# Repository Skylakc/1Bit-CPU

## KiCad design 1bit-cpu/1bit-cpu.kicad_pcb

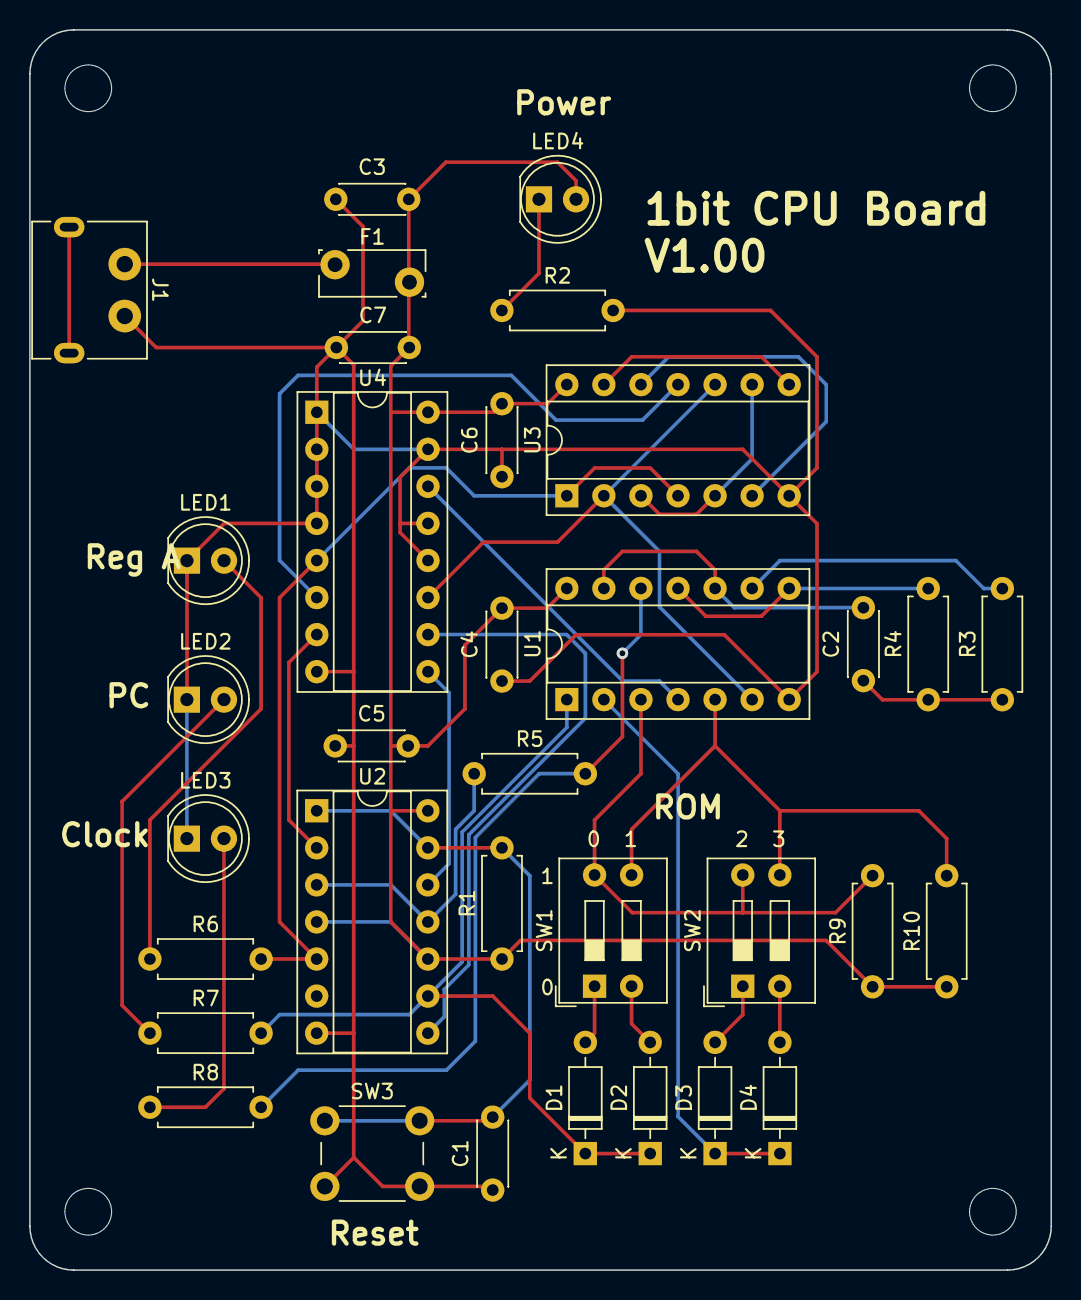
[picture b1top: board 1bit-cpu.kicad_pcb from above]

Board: 2 copper layers, 70.0 x 85.0 mm, 38 parts (0 on the bottom side), 32 nets.

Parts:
C1, C4, C5, C6, C7: 0.1u; C_Disc_D4.3mm_W1.9mm_P5.00mm
C2: 10μ; C_Disc_D4.3mm_W1.9mm_P5.00mm
C3: 10u; C_Disc_D4.3mm_W1.9mm_P5.00mm
D1, D2, D3, D4: 1N4148; D_DO-35_SOD27_P7.62mm_Horizontal
F1: 100mA; Fuse_Bourns_MF-RG300
H1, H2, H3, H4: M3; MountingHole_3.2mm_M3
J1: USBTypeC; USB_C_PowerOnly
LED1, LED2, LED3, LED4: LED; LED_D5.0mm
R1, R5, R9, R10: 10k; R_Axial_DIN0207_L6.3mm_D2.5mm_P7.62mm_Horizontal
R2, R6, R7, R8: 1k; R_Axial_DIN0207_L6.3mm_D2.5mm_P7.62mm_Horizontal
R3: 100k; R_Axial_DIN0207_L6.3mm_D2.5mm_P7.62mm_Horizontal
R4: 47k; R_Axial_DIN0207_L6.3mm_D2.5mm_P7.62mm_Horizontal
SW1, SW2: SW; SW_DIP_SPSTx02_Slide_9.78x7.26mm_W7.62mm_P2.54mm
SW3: SW_Push; SW_PUSH_6mm
U1: 74HC04; DIP-14_W7.62mm_Socket
U2: 74HC74; DIP-14_W7.62mm_Socket
U3: 74HC00; DIP-14_W7.62mm_Socket
U4: 74HC153; DIP-16_W7.62mm_Socket

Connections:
+5V: C3.2, C4.2, C5.2, C6.2, C7.2, F1.2, LED4.2 (A), R1.1, R9.1, R10.1, U1.14 (VCC), U2.4 (~S), U2.10 (~S), U2.14 (VCC), U3.14 (VCC), U4.16 (VCC)
GND: C1.1, C3.1, C4.1, C5.1, C6.1, C7.1, J1.A12 (GND), LED1.1 (K), LED2.1 (K), LED3.1 (K), R2.2, SW3.2, U1.7 (GND), U2.7 (GND), U3.7 (GND), U4.1 (1G), U4.2 (B), U4.3 (1C3), U4.4 (1C2), U4.8 (GND), U4.12 (2C2), U4.13 (2C3), U4.15 (2G)
unnamed: C2.1, R3.1, R4.1
unnamed: C2.2, U1.10, U1.13
unnamed: D1.2 (A), SW1.1
unnamed: D1.1 (K), D2.1 (K), R7.2, U1.1, U2.9 (Q)
unnamed: D2.2 (A), SW1.2
unnamed: D3.2 (A), SW2.1
unnamed: D3.1 (K), D4.1 (K), U1.2
unnamed: D4.2 (A), SW2.2
unnamed: F1.1, J1.A9 (VBUS)
unnamed: LED1.2 (A), R6.1
unnamed: LED2.2 (A), R7.1
unnamed: LED3.2 (A), R8.1
unnamed: LED4.1 (K), R2.1
unnamed: R3.2, U1.9
unnamed: R4.2, U1.8, U1.11
unnamed: R5.2, R8.2, U1.12
unnamed: R9.2, SW1.4, SW2.4, U1.3
unnamed: R10.2, SW1.3, SW2.3, U1.5
unnamed: R5.1, U2.3 (C), U2.11 (C)
unnamed: U2.2 (D), U4.7 (Y1)
unnamed: R6.2, U2.5 (Q), U3.1, U3.4, U4.5 (1C1)
unnamed: C1.2, R1.2, SW3.1, U2.1 (~R), U2.13 (~R)
unnamed: U2.12 (D), U4.9 (Y2)
unnamed: U2.8 (~Q), U4.10 (2C0)
unnamed: U3.3, U3.5, U3.9
unnamed: U3.6, U3.12
unnamed: U3.8, U3.13
unnamed: U3.11, U4.6 (1C0)
unnamed: U1.6, U3.2, U3.10, U4.11 (2C1)
unnamed: U1.4, U4.14 (A)

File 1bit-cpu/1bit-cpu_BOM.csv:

"Reference","Value","Datasheet","Footprint","Qty","DNP"
"C1,C4,C5,C6,C7","0.1u","~","Capacitor_THT:C_Disc_D4.3mm_W1.9mm_P5.00mm","5",""
"C2,C3","10u","~","Capacitor_THT:C_Disc_D4.3mm_W1.9mm_P5.00mm","2",""
"D1,D2,D3,D4","1N4148","https://assets.nexperia.com/documents/data-sheet/1N4148_1N4448.pdf","Diode_THT:D_DO-35_SOD27_P7.62mm_Horizontal","4",""
"F1","100mA","~","Fuse:Fuse_Bourns_MF-RG300","1",""
"H1,H2,H3,H4","MountingHole","~","MountingHole:MountingHole_3.2mm_M3","4",""
"J1","USB_C_Receptacle_PowerOnly_6P","https://www.usb.org/sites/default/files/documents/usb_type-c.zip","Library:USB_C_PowerOnly","1",""
"LED1,LED2,LED3,LED4","LED","~","LED_THT:LED_D5.0mm","4",""
"R1,R5,R9,R10","10k","~","Resistor_THT:R_Axial_DIN0207_L6.3mm_D2.5mm_P7.62mm_Horizontal","4",""
"R2,R6,R7,R8","1k","~","Resistor_THT:R_Axial_DIN0207_L6.3mm_D2.5mm_P7.62mm_Horizontal","4",""
"R3","100k","~","Resistor_THT:R_Axial_DIN0207_L6.3mm_D2.5mm_P7.62mm_Horizontal","1",""
"R4","47k","~","Resistor_THT:R_Axial_DIN0207_L6.3mm_D2.5mm_P7.62mm_Horizontal","1",""
"SW1,SW2","SW","~","Button_Switch_THT:SW_DIP_SPSTx02_Slide_9.78x7.26mm_W7.62mm_P2.54mm","2",""
"SW3","SW_Push","~","Button_Switch_THT:SW_PUSH_6mm","1",""
"U1","74HC04","https://assets.nexperia.com/documents/data-sheet/74HC_HCT04.pdf","Package_DIP:DIP-14_W7.62mm_Socket","1",""
"U2","74HC74","74xx/74hc_hct74.pdf","Package_DIP:DIP-14_W7.62mm_Socket","1",""
"U3","74HC00","http://www.ti.com/lit/gpn/sn74hc00","Package_DIP:DIP-14_W7.62mm_Socket","1",""
"U4","74HC153","http://www.ti.com/lit/gpn/sn74LS153","Package_DIP:DIP-16_W7.62mm_Socket","1",""

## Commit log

2024-06-01 new file: 1bit-cpu/1bit-cpu-rescue.kicad_sym new file: 1bit-cpu/1bit-cpu.kicad_pcb new file: 1bit-cpu/1bit-cpu.kicad_prl new file: 1bit-cpu/1bit-cpu.kicad_pro new file: 1bit-cpu/1bit-cpu.kicad_sch ne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
2024-06-02 写了一点教程
2024-06-02 更新图片
2024-06-02 删除无效文件
